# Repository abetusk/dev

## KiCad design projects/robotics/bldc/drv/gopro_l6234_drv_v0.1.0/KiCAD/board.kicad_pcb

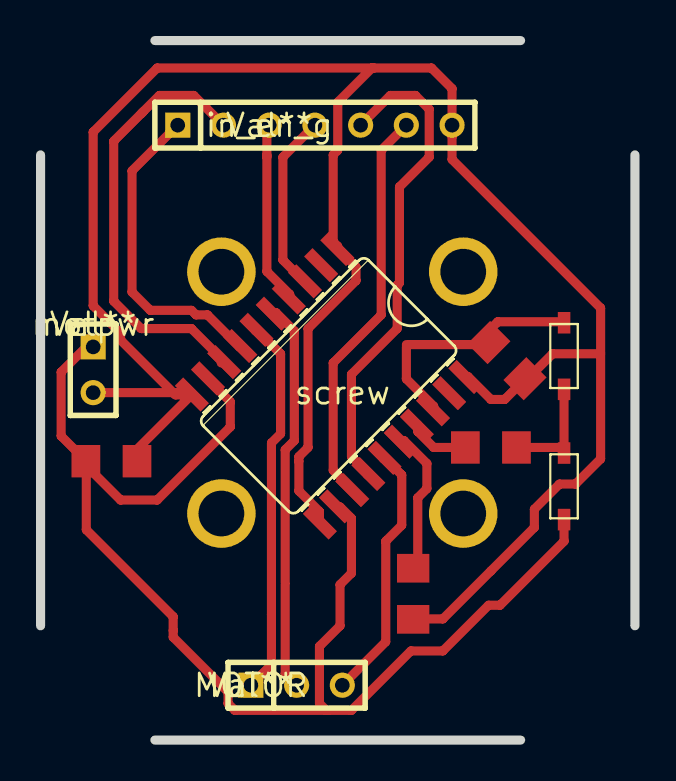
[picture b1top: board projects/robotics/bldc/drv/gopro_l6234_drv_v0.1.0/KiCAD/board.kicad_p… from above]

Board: 5 copper layers, 33.0 x 38.9 mm, 10 parts (0 on the bottom side), 13 nets.

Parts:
C1: 1uf; C1206
C2: 10nf; C1206
C3: .22uf; C1206
D0, D1: 1n4148; SOD-123
MOTOR: Val**; SIL-3
U0: l6234; SO20W
c0: .1uf; C1206
in_en_g: Val**; SIL-7
motpwr: Val**; SIL-2

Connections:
unnamed: D0.C, U0.1, U0.11, in_en_g.7
unnamed: U0.3, in_en_g.4
unnamed: MOTOR.2, U0.5
unnamed: U0.6, U0.12
unnamed: U0.7, in_en_g.3
unnamed: U0.8, in_en_g.2
unnamed: U0.13, in_en_g.6
unnamed: MOTOR.3, U0.15
unnamed: C3.1, U0.16
unnamed: C2.2, U0.17
unnamed: C3.2, U0.9, U0.20
unnamed: C2.1, D1.A
unnamed: U0.10, c0.2, motpwr.2

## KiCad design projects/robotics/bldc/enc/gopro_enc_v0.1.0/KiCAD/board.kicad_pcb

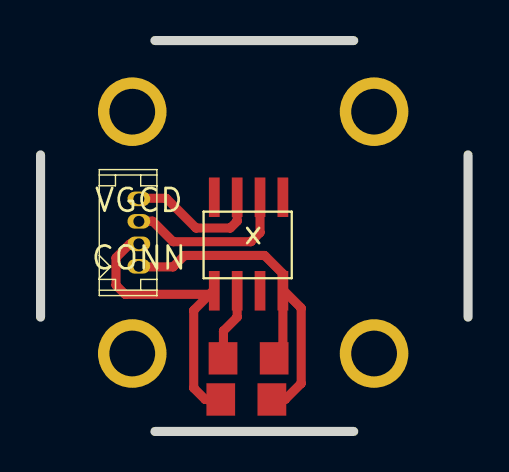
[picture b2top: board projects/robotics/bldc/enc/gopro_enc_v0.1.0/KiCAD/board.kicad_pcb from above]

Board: 5 copper layers, 23.7 x 21.7 mm, 5 parts (0 on the bottom side), 5 nets.

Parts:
C0: 100nF; C1206
C1: 1uF; C1206
CONN: VGCD; MOLEX_53047-0410_4PIN_VERT
enc: as5600; SOIC-8
x: meow_gopro_bot_screw

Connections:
unnamed: C1.1, enc.2
unnamed: CONN.4, enc.7
unnamed: C0.1, CONN.2, enc.1
unnamed: C0.2, C1.2, CONN.1, enc.4
unnamed: CONN.3, enc.6

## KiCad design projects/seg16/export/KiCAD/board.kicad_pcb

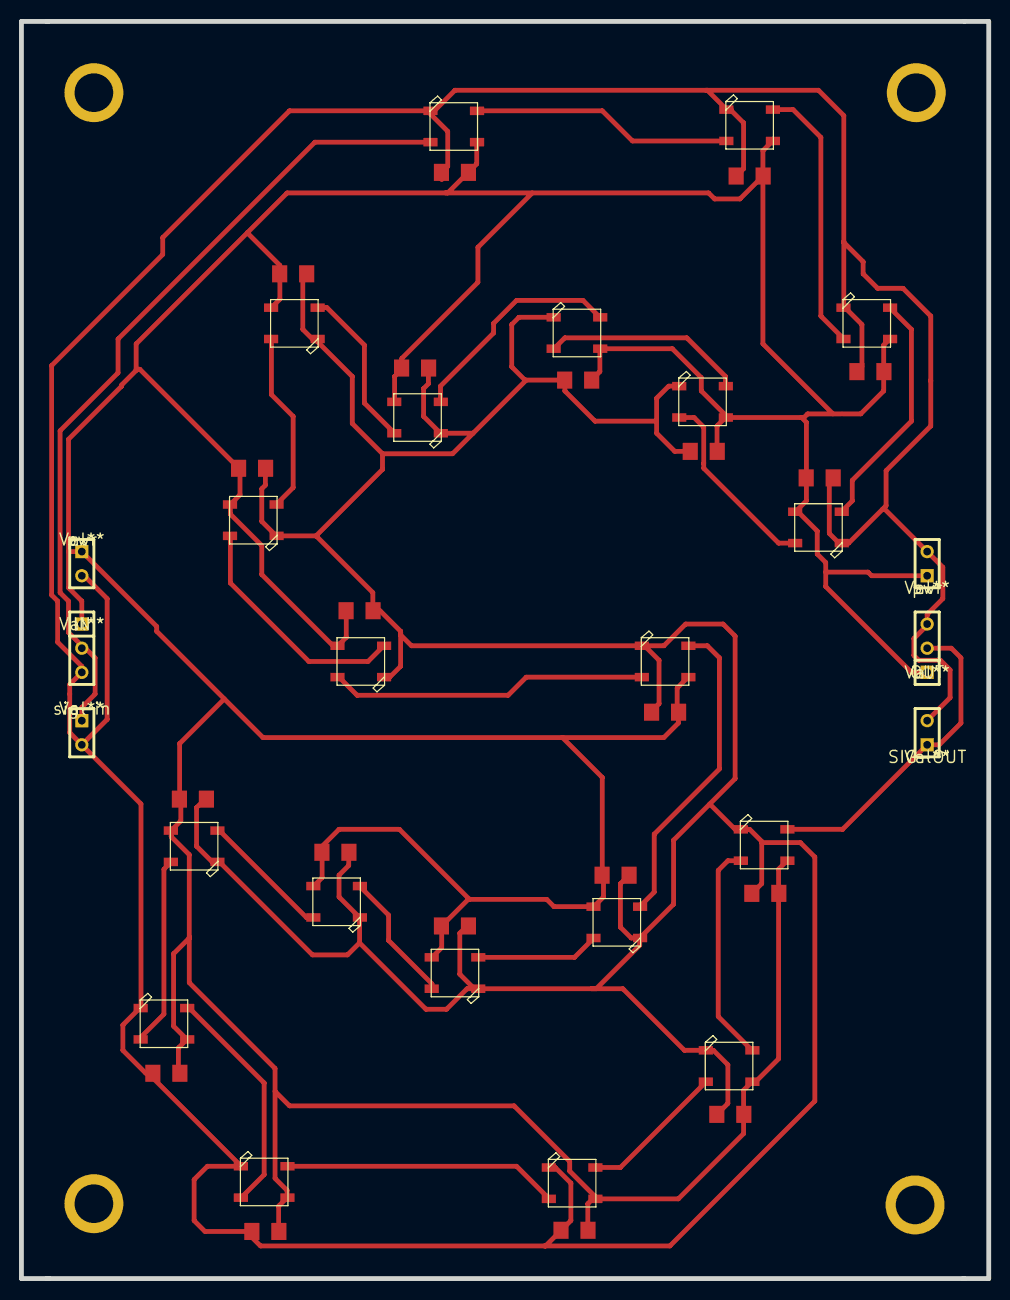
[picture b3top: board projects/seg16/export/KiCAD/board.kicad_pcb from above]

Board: 5 copper layers, 101.7 x 132.2 mm, 46 parts (0 on the bottom side), 23 nets.

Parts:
C2, C3, C4, C5, C6, C7, C8, C9, C10, C11, C12, C13, C14, C15, C16, C17, C18, C19, C20: C; C1206
IN: Val**; SIL-3
OUT: Val**; SIL-3
SIG-OUT: Val**; SIL-2
U3, U6, U7, U8, U9, U10, U11, U12, U13, U14, U15, U16, U17, U18, U19, U20, U21, U22, U23: WS2812B; meowWS2812B
a0: WS2812B; meowWS2812B
aC0: 100nf; C1206
pwr: Val**; SIL-2
pwr#2: Val**; SIL-2
sig-in: Val**; SIL-2

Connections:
unnamed: OUT.2, SIG-OUT.1, U8.2-DOUT
unnamed: C2.2, C3.2, C4.2, C5.2, C6.2, C7.2, C8.2, C9.2, C10.2, C11.2, C12.2, C13.2, C14.2, C15.2, C16.2, C17.2, C18.2, C19.2, C20.2, IN.3, OUT.3, SIG-OUT.2, U3.3-GND, U6.3-GND, U7.3-GND, U8.3-GND, U9.3-GND, U10.3-GND, U11.3-GND, U12.3-GND, U13.3-GND, U14.3-GND, U15.3-GND, U16.3-GND, U17.3-GND, U18.3-GND, U19.3-GND, U20.3-GND, U21.3-GND, U22.3-GND, U23.3-GND, a0.3-GND, aC0.2, pwr.2, pwr#2.2, sig-in.2
unnamed: C2.1, C3.1, C4.1, C5.1, C6.1, C7.1, C8.1, C9.1, C10.1, C11.1, C12.1, C13.1, C14.1, C15.1, C16.1, C17.1, C18.1, C19.1, C20.1, IN.1, OUT.1, U3.1-VDD, U6.1-VDD, U7.1-VDD, U8.1-VDD, U9.1-VDD, U10.1-VDD, U11.1-VDD, U12.1-VDD, U13.1-VDD, U14.1-VDD, U15.1-VDD, U16.1-VDD, U17.1-VDD, U18.1-VDD, U19.1-VDD, U20.1-VDD, U21.1-VDD, U22.1-VDD, U23.1-VDD, a0.1-VDD, aC0.1, pwr.1, pwr#2.1
unnamed: U3.4-DIN, a0.2-DOUT
unnamed: IN.2, a0.4-DIN, sig-in.1
unnamed: U3.2-DOUT, U6.4-DIN
unnamed: U6.2-DOUT, U7.4-DIN
unnamed: U7.2-DOUT, U20.4-DIN
unnamed: U9.4-DIN, U10.2-DOUT
unnamed: U10.4-DIN, U11.2-DOUT
unnamed: U11.4-DIN, U12.2-DOUT
unnamed: U12.4-DIN, U13.2-DOUT
unnamed: U15.4-DIN, U18.2-DOUT
unnamed: U14.4-DIN, U15.2-DOUT
unnamed: U16.2-DOUT, U17.4-DIN
unnamed: U17.2-DOUT, U21.4-DIN
unnamed: U18.4-DIN, U19.2-DOUT
unnamed: U19.4-DIN, U20.2-DOUT
unnamed: U21.2-DOUT, U22.4-DIN
unnamed: U22.2-DOUT, U23.4-DIN
unnamed: U14.2-DOUT, U16.4-DIN
unnamed: U13.4-DIN, U23.2-DOUT
unnamed: U8.4-DIN, U9.2-DOUT
